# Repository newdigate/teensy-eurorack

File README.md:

# teensy eurorack audio shield 

[![built with kicad](https://img.shields.io/badge/project-v5.1.6-brightgreen.svg?label=kicad&colorA=555555&colorB=8a8fff&logo=
)](https://kicad.org/)

Sponsored by:

**open source [hardware](hardware) and [software](https://github.com/newdigate/teensy-eurorack-software) for a 30-channel (14 in / 16 out) 16-bit analog [teensy 4.1](https://www.pjrc.com/store/teensy40.html "teensy 4.1 board") eurorack shield** 

* add peripherals to extend your [teensy 4.1](https://www.pjrc.com/store/teensy40.html "teensy 4.1 board") to interface with 
  * analog line audio (6 in / 8 out)
  * analog control voltages (8 in / 8 out: -10 to +10 volts)
  * midi in/out
  * microSD socket breakout
  * USB-A host and USB-B devices
  * 4 potentiometers, 3 encoders w/switch
* online designer [teensy eurorack audio gui](https://newdigate.github.io/teensy-eurorack-audio-gui) [^](https://github.com/newdigate/teensy-eurorack-audio-gui)

# updates 
  * 14 August 2021 : software and examples have moved to this repo [newdigate/teensy-eurorack-software](https://github.com/newdigate/teensy-eurorack-software)

# contents
* [sponsor](#sponsor)
* [specifications](#specifications)
* [license](#license)
* [open source software-stack](#open-source-software-stack)
* [build](#build)
  * [order pcbs](#order-pcbs)
  * [sourcing parts](#sourcing-parts)
    * [mouser boms](#mouser-boms)
    * [parts not on mouser boms](#parts-not-on-mouser-boms)
  * [interactive html boms online](#interactive-html-boms-online)
* [source code](#source-code)
* [improvements](#improvements)
* [printed circuit boards](#printed-circuit-boards)
  * [mainboard](#mainboard)
  * [breakout board](#breakout-board)
* [schematics](#schematics)  
* [panel design](#panel-design)  
* [assembly technical drawings](#assembly-technical-drawings)
* [youtube videos](#youtube-videos)
* [versions](#versions)
* [todo](#todo)
* [continuous-integration](#continuous-integration)
* [credits](#credits)
* [sponsored by](#sponsored-by)

# sponsor
* [patreon/teensy_eurorack](https://www.patreon.com/teensy_eurorack)
* paypal.me: [paypal.me/nicnewdigate](https://paypal.me/nicnewdigate)

# specifications
* **microcontrollers:** 
  * 600 Mhz ARM cortex m7 ( [teensy 4.1 board](https://www.pjrc.com/store/teensy41.html "teensy 4.1 board") )
* **audio:** multi-channel audio codec ( 6-in / 8-out 24-bit sound card - [CS42448](https://statics.cirrus.com/pubs/proDatasheet/CS42448_F5.pdf) )
  * *the audio codec circuit originally started as a discussion on quad audio channel outputs and a pcb design integrating teensy and cs42448 from Paul Stoffregen on [pjrc forum](https://forum.pjrc.com/threads/41371-Quad-channel-output-on-Teensy-3-6?p=138828&viewfull=1#post138828)*
* **analog control voltage ins/outs:** -10V to 10V 16bit/sample, 8 x inputs and 8 x outputs ( [ad7606](https://www.analog.com/media/en/technical-documentation/data-sheets/ad7606_7606-6_7606-4.pdf), 2x [ad5754](https://www.analog.com/media/en/technical-documentation/data-sheets/AD5724_5734_5754.pdf) )
* **display:** ST7735 128x128 16bit-color tft display
* **breakouts:** 
  * microSD card socket, 
  * USB host/device, 
  * midi in/out, 
  * knobs (4 x pots, 3 x encoders w/switch)
* **panel:** 24HP aluminium panel mounted for eurorack case
* **programability**: 
  * write arduino compatible c/c++ firmware & program using arduino/teensyduino
  * arm gnu toolchain [downloads](https://developer.arm.com/tools-and-software/open-source-software/developer-tools/gnu-toolchain/gnu-rm/downloads)
  * teensy [audio library](https://www.pjrc.com/teensy/gui/)

# license
* All artifacts are MIT license unless otherwise specified on a per file basis.

# open source software stack
* All [schematics](hardware/CIRCUITS.md) and boards are created using [Kicad](https://kicad.org/) 
* All mechanical designs are created using [FreeCAD](https://github.com/FreeCAD/FreeCAD)
* Some images have been rendered using [Blender 2.81](https://www.blender.org/)

# build
## order pcbs
* Use these gerber files to order 3 pcboards
  * the uSD-card extender should be about 0.6mm - 0.8mm thick
  * if you're using solder paste, you'll need to order the stencils of the bottom-side of main- and breakout boards.   
  
* [gerbers-breakout.zip](https://github.com/newdigate/teensy-eurorack/raw/master/hardware/gerbers/gerbers-breakout.zip)
* [gerbers-mainboard.zip](https://github.com/newdigate/teensy-eurorack/raw/master/hardware/gerbers/gerbers-mainboard.zip)
* [gerbers-uSD_extender_male.zip](https://github.com/newdigate/teensy-eurorack/raw/master/hardware/gerbers/gerbers-uSD_extender_male.zip)

## sourcing parts
Most parts are available from mouser.com - you can use the mouser BOMs below as a template to create an order. 

### mouser boms
* [mainboard](https://eu.mouser.com/ProjectManager/ProjectDetail.aspx?AccessID=e554cc1725)
* [breakoutboard](https://www.mouser.com/ProjectManager/ProjectDetail.aspx?AccessID=76e89a9e69)
### parts not on mouser boms
* panel: 
  * order from Front Panel Express: [.fpd](https://github.com/newdigate/teensy-eurorack/tree/master/hardware/panel/fpd)
    * for US: download [Front Panel Express](https://www.frontpanelexpress.com)
    * for Europe: download [Front Panel Designer](https://www.schaeffer-ag.de/en/front-panel-designer)
  * CNC your own with [FreeCad](https://www.freecadweb.org/downloads.php): [panel.FCStd](https://github.com/newdigate/teensy-eurorack/blob/master/hardware/panel/panel.FCStd) 
* mainboard:
  * 2.54mm pitch pin headers and sockets
    * J28: Eurorack power header: either male or female (2 x 8), I use female as my eurorack power (tip top) has male connectors. 
* breakout:
  * uSD card socket: [pjs008u-3000-0 yamaichi](https://octopart.com/pjs008u-3000-0-yamaichi-20649952?r=sp)
  * display: ST7735 (1.44 inch TFT LCD ST7735 SPI display module 128*128 8pin 65K color)

  * 16 x thonkiconns: [PJ398SM](https://www.thonk.co.uk/shop/thonkiconn)
  * 4 x 9mm snap-in pots: [alpha-9mm-pots](https://www.thonk.co.uk/shop/alpha-9mm-pots/) - You want linear (B-series) not audio (A-series) B5K or B10K should be ideal.
  * 3 x rotary encoders w/switches: Half axis (D-shaft) rotary encoder, handle/axis length: 20mm, EC11/EC12 digital potentiometer with switch - 5Pin

**Update**: USB-A-S-X-X-VT is no longer available. [Amphenol Commercial Products GSB11111ALF](https://mou.sr/3OmC2OO) looks like it may be a good replacement.

## interactive html boms online
  * [mainboard](https://newdigate.github.io/teensy-eurorack/teensy-eurorack)
  * [breakoutboard](https://newdigate.github.io/teensy-eurorack/teensy-eurorack-breakout)

# source code
 * Teensy Audio library drivers for ad5754, ad7606 via SPI
   * [teensy-audio-ad5754-ad7606](https://github.com/newdigate/teensy-audio-ad5754-ad7606)
 * simple standard midi file reader 
   * [midi-smf-reader](https://github.com/newdigate/midi-smf-reader)
 * generic sequencer
   * [teensy-quencer](https://github.com/newdigate/teensy-quencer)
 * variable rate playback
   * [teensy-variable-playback](https://github.com/newdigate/teensy-variable-playback)
 * oscilliscope and x/y scope display components
   * [teensy-audio-libtftscope](https://github.com/newdigate/teensy-audio-libtftscope)
 * cmake macros for compiling c++ for arm cortex 
   * [teensy-cmake-macros](https://github.com/newdigate/teensy-cmake-macros)
 * Audio level and CV level meters 
   * [teensy-audio-display-components](https://github.com/newdigate/teensy-audio-display-components)

# improvements
At this point Im just focusing on finalising/polishing the current version, but there are some improvements I'd like to make at some point.
* add 4x jack sockets for analog output of knobs on breakout board. 
* use 3.5mm jack sockets (as well as standard midi din connectors) for midi in and out. 
* switch to active audio input and output circuitry, allow switchable 0dB / 12dB gain, for guitar signals.
* let me know if you're think there something else that can be improved, added, removed. 

There is a journal of my progress (its a bit out of date, sorry) - [journal.md](hardware/JOURNAL.md) 

**What you can do if you like to see progress with this project?**
* [#sponsor](#sponsor)...
* star this repository (means you need a github account - go for it!!)
* subscribe [Nic N on youtube](https://www.youtube.com/channel/UChMicDp8wUXYzBhEN-Wvb5g) 
* download kicad and freecad, clone this repo, make improvements, commit & send pull-requests, and raise issues...

# printed circuit boards
## [mainboard](hardware/boards/mainboard) 
* standard double layer printed circuit board
  * thinkness: 1.6mm  
  * minimum trace: 6 mil
  * minimum clearance: 6 mil
  * dimension: 118mm*102mm
* socket to connect teensy 4.0 board
* cs42448 audio codec 
* 3 x stereo 6.35mm TRS jack inputs
* 4 x stereo 6.35mm TRS jack outputs
* pin sockets to connect breakout board

## breakout board
* 2 layer printed circuit board
  * thinkness: 1.6mm  
  * minimum trace: 6 mil
  * minimum clearance: 6 mil
  * dimension: 110mm*111mm
* 8 x 3.5mm jack socket for analog control voltage inputs
* 8 x 3.5mm jack socket for analog control voltage outputs
* midi in/out DIN sockets
* usb device/host
  * USB-B: USB device mode
  * USB-A: USB host mode
* micro-SD card socket
* 4 x linear pots
* 3 x rotary encoders with switches 

# schematics

# [panel design](hardware/panel)

# assembly technical drawings 

# youtube videos 
* [Nic N](https://www.youtube.com/channel/UChMicDp8wUXYzBhEN-Wvb5g) 
  * [youtube: Assembling custom eurorack audio shield for teensy 4.1](https://www.youtube.com/watch?v=PzaJ3Wq1Fsc)
  * [youtube: Teensy 4.0 eurorack shield design intro](https://www.youtube.com/watch?v=aNUSEszbnYU)
  * [youtube: 0v to 10v control voltage input, output and display using teensy 4.0](https://www.youtube.com/watch?v=5d5x8F7HRko)
  * [youtube: DIY assembly build - teensy 4.0 eurorack audio module](https://www.youtube.com/watch?v=oZzPgpTrEhc)
  * [youtube: assembly teensy eurorack shield](https://www.youtube.com/watch?v=Jx2KgpoT3WY)
  * [youtube: assembly timelapse](https://www.youtube.com/watch?v=s-514rDjirY)
  * [youtube: Eurorack digital audio modules powered by teensy micro-controller](https://www.youtube.com/watch?v=6zt6OF7UOTc)
  * [youtube: side-channel stereo audio separation with teensy 4.0](https://www.youtube.com/watch?v=N0IBevm4hTQ)

# versions
## v2.1 (Saturday 3 April 2021)
* **Improvement**: Mainboard: Tie LRCLK pin 20 to pin40 to sync DAC/ADC sampling w/ audio sampling
* **FIXED**: breakout: add 1k pull-up resistor to MIDI rx pin
* mainboard: silkscreen: add Kicad OpenSourceHardware logo
* breakout: silkscreen: add Kicad OpenSourceHardware logo

## v2.0.3 (Saturday 13/02/2021)
* breakout: st7735 display changed vcc, reset, backlight from 5v to 3v3.

## v2.0.2 (31/01/2021)
* Mainboard: spaced out traces as there appeared to be some interference under certain circumstances.

## v2.0.1 (27/01/2021) 
* Mainboard: add daisy chain TX/RX connector on back side to communicate between multiple boards
* Breakout board: changed back to double layer board.

## v2.0.0(b)
* Breakout board: Corrected polarity of +-12V pin headers on breakout board (ouch!!!)
* change ADC to use external 2.5v voltage reference, same as DAC voltage reference now 

## v2.0.0
* SPI: separated ADC, DAC from display: 
  * st7735 display has its own dedicated SPI - (SPI0, stays the same)
  * ADC / DAC are now sharing SPI1
* integrated ADC and DAC into teensy audio library.
* added one more ad5754 DAC for total of 8 control voltage analog output channels

## v1.9.1b
* mainboard: correction: reconnected LRCLK to codec.

## v1.9.1
* connected DAC_SCK output (pin 19) to pin 31
  * allow cable select to be asserted on minor spi data cycle after every 24 or 48 spi clock cycles, using interrupt on pin 31.
    * hopefully this will allow DMA spi transfers to AD5754 and which will make integration with teensy audio library much easier

## v1.9 
updated to teesy 4.1 and improvements to make easier to build
* updated from teensy 4.0 to teensy 4.1
* schematic, footprint and pcb clean-up 
  * replaced footprints imported from eagle with native kicad footprints
* removed atmel samd21 and gpio ICs
* replaced gpio with AD5754 (extra 4 DAC channels)
* replaced RGB encoders with regular encoders
* replaced analog-GND-to-digital-GND footprint with a 0805 zero ohm resistor footprint. (DRC checks can pass now...)
* (temporarily) removed serial TX/RX to unused eurorack power pins
  
# todo 
- [x] ~~finalize design / circuits / boards~~
- [x] ~~order~~ (v.2.1)
- [x] ~~assemble~~
- [x] ~~testing~~
  - [x] ~~CS42448 audio codec~~
    - [x] ~~Audio input~~
    - [x] ~~Audio output~~
  - [x] ~~control voltage input~~
  - [x] ~~control voltage output~~
  - [x] ~~usb host~~
  - [x] ~~usb device~~
  - [x] ~~midi in~~
  - [x] ~~midi out~~
  - [x] ~~st7735 display~~
  - [x] ~~sd card extension & adapter~~
- [ ] Document 
  - [ ] order & build process
  - [ ] software process
- [ ] Firmware

# continuous-integration 
* testing automated build and packaging 
* [github.com/pwuertz/kicad_picknplace_assistant](https://github.com/pwuertz/kicad_picknplace_assistant)
* [github.com/productize/kicad-automation-scripts](https://github.com/productize/kicad-automation-scripts)
* [InteractiveHtmlBom](https://github.com/openscopeproject/InteractiveHtmlBom) by [openscopeproject](https://github.com/openscopeproject)

# credits 
* https://github.com/dgouramanis/usdextendercable

# sponsored by
Massive thanks to these generous people who have provided support!
* Hannes Schnaitter
* Daniel Hengeveld [thedaniel on github](https://github.com/thedaniel)
* Derek Brost
* Martin Eigel
* Morgan Massens

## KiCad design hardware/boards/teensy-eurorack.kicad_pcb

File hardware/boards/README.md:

# boards
 * [mainboard](#mainboard)
 * [breakout](#breakout)
 
All circuit boards are standard double layer boards with minimum 6 mil clearance and 6 mil traces. 

I have been using jlcpcb to fabricate my circuit boards.  

## [mainboard](mainboard) 

[mainboard design files](mainboard)

### [breakout](knobs-controller) 

[breakout design files](knobs-controller)

# assembly technical drawings

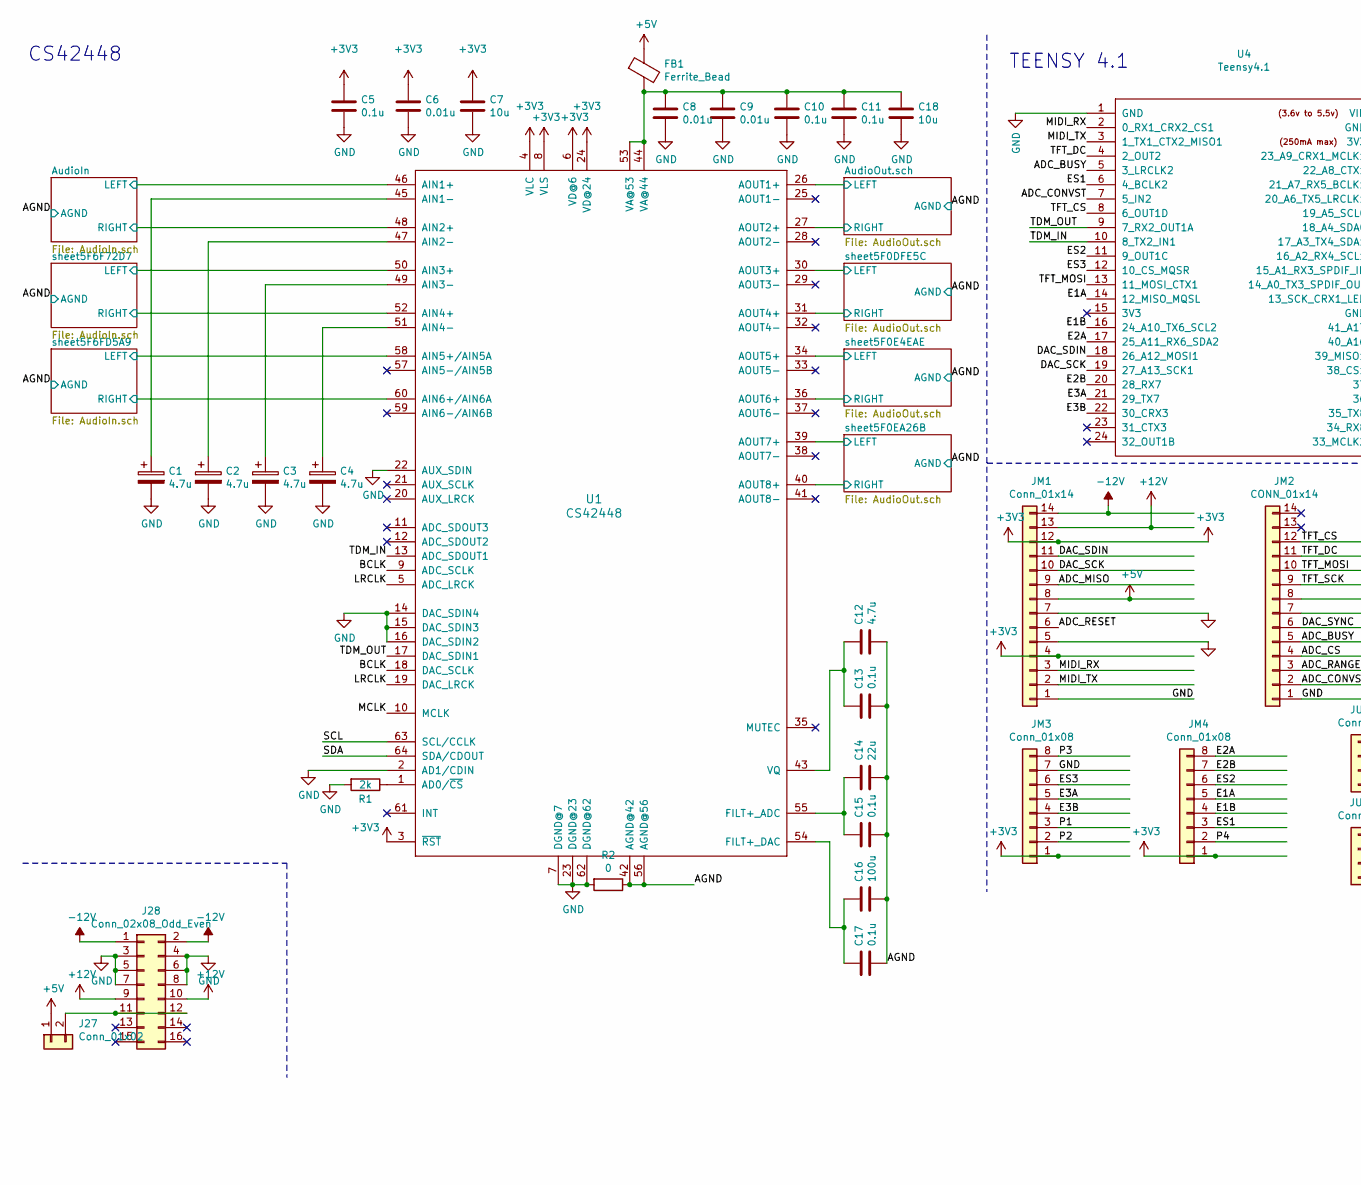
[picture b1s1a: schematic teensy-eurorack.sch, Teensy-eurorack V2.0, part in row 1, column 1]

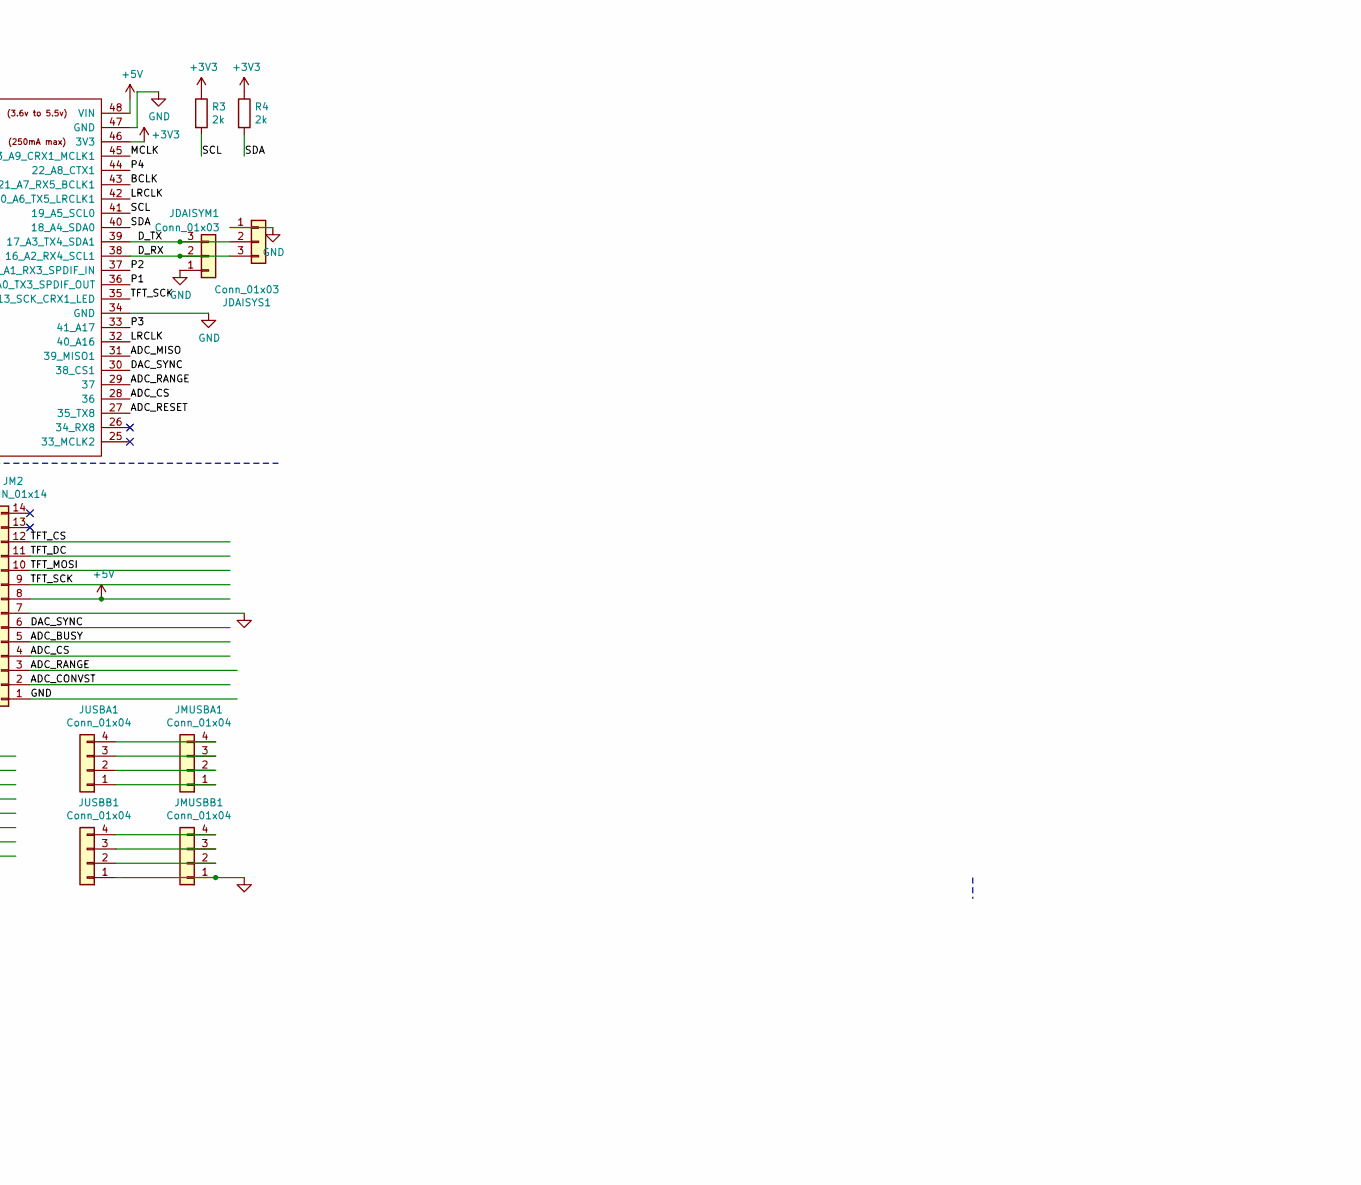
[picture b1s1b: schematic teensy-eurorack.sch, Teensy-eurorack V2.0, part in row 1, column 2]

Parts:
C1, C2, C3, C4: 4.7u; CP_Radial_D5.0mm_P2.50mm
C5, C10, C11, C13, C15, C17: 0.1u; C_0805_2012Metric
C6, C8, C9: 0.01u; C_0805_2012Metric
C7, C18: 10u; C_0805_2012Metric
C12: 4.7u; C_0805_2012Metric
C14: 22u; C_0805_2012Metric
C16: 100u; C_1206_3216Metric
FB1: Ferrite_Bead; L_0603_1608Metric
J27: Conn_01x02; PinHeader_1x02_P2.54mm_Vertical
J28: Conn_02x08_Odd_Even; PinHeader_2x08_P2.54mm_Vertical
JDAISYM1: Conn_01x03; PinHeader_1x03_P2.54mm_Vertical
JDAISYS1: Conn_01x03; PinHeader_1x03_P2.54mm_Vertical
JM1: Conn_01x14; PinHeader_1x14_P2.54mm_Vertical
JM2: CONN_01x14; PinHeader_1x14_P2.54mm_Vertical
JM3, JM4: Conn_01x08; PinHeader_1x08_P2.54mm_Vertical
JMUSBA1: Conn_01x04; PinHeader_1x04_P2.54mm_Vertical
JMUSBB1: Conn_01x04; PinHeader_1x04_P2.54mm_Vertical
JUSBA1: Conn_01x04; PinHeader_1x04_P2.54mm_Vertical
JUSBB1: Conn_01x04; PinHeader_1x04_P2.54mm_Vertical
R1, R3, R4: 2k; R_0805_2012Metric
R2: 0; R_0805_2012Metric
U1: CS42448; LQFP-64_10x10mm_P0.5mm
U4: Teensy4.1; Teensy41_tht

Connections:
+3V3: C5.1, C6.1, C7.1, JM1.4, JM1.12, JM3.1, JM4.1, R3.1, R4.1, U1.3 (~RST~), U1.4 (VLC), U1.6 (VD@6), U1.8 (VLS), U1.24 (VD@24), U4.46 (3V3)
+5V: FB1.1, J27.1, JM1.8, JM2.8, U4.48 (VIN)
+12V: J28.9, J28.10, JM1.13
-12V: J28.1, J28.2, JM1.14
/ADC_BUSY: JM2.5, U4.5 (3_LRCLK2)
/ADC_CONVST: JM2.2, U4.7 (5_IN2)
/ADC_CS: JM2.4, U4.28 (36)
/ADC_MISO: JM1.9, U4.31 (39_MISO1)
/ADC_RANGE: JM2.3, U4.29 (37)
/ADC_RESET: JM1.6, U4.27 (35_TX8)
/AGND: C12.2, C13.2, C14.2, C15.2, C16.2, C17.2, R2.1, U1.42 (AGND@42), U1.56 (AGND@56); also elsewhere on the board
/AudioIn/LEFT: U1.46 (AIN1+); also elsewhere on the board
/AudioIn/RIGHT: U1.48 (AIN2+); also elsewhere on the board
/AudioOut.sch/LEFT: U1.26 (AOUT1+); also elsewhere on the board
/AudioOut.sch/RIGHT: U1.27 (AOUT2+); also elsewhere on the board
/BCLK: U1.9 (ADC_SCLK), U1.18 (DAC_SCLK), U4.43 (21_A7_RX5_BCLK1)
/DAC_SCK: JM1.10, U4.19 (27_A13_SCK1)
/DAC_SDIN: JM1.11, U4.18 (26_A12_MOSI1)
/DAC_SYNC: JM2.6, U4.30 (38_CS1)
/D_RX: JDAISYM1.2, JDAISYS1.3, U4.38 (16_A2_RX4_SCL1)
/D_TX: JDAISYM1.3, JDAISYS1.2, U4.39 (17_A3_TX4_SDA1)
/E1A: JM4.5, U4.14 (12_MISO_MQSL)
/E1B: JM4.4, U4.16 (24_A10_TX6_SCL2)
/E2A: JM4.8, U4.17 (25_A11_RX6_SDA2)
/E2B: JM4.7, U4.20 (28_RX7)
/E3A: JM3.5, U4.21 (29_TX7)
/E3B: JM3.4, U4.22 (30_CRX3)
/ES1: JM4.3, U4.6 (4_BCLK2)
/ES2: JM4.6, U4.11 (9_OUT1C)
/ES3: JM3.6, U4.12 (10_CS_MQSR)
/LRCLK: U1.5 (ADC_LRCK), U1.19 (DAC_LRCK), U4.32 (40_A16), U4.42 (20_A6_TX5_LRCLK1)
/MCLK: U1.10 (MCLK), U4.45 (23_A9_CRX1_MCLK1)
/MIDI_RX: JM1.3, U4.2 (0_RX1_CRX2_CS1)
/MIDI_TX: JM1.2, U4.3 (1_TX1_CTX2_MISO1)
/P1: JM3.3, U4.36 (14_A0_TX3_SPDIF_OUT)
/P2: JM3.2, U4.37 (15_A1_RX3_SPDIF_IN)
/P3: JM3.8, U4.33 (41_A17)
/P4: JM4.2, U4.44 (22_A8_CTX1)
/SCL: R3.2, U1.63 (SCL/CCLK), U4.41 (19_A5_SCL0)
/SDA: R4.2, U1.64 (SDA/CDOUT), U4.40 (18_A4_SDA0)
/TDM_IN: U1.13 (ADC_SDOUT1), U4.10 (8_TX2_IN1)
/TDM_OUT: U1.17 (DAC_SDIN1), U4.9 (7_RX2_OUT1A)
/TFT_CS: JM2.12, U4.8 (6_OUT1D)
/TFT_DC: JM2.11, U4.4 (2_OUT2)
/TFT_MOSI: JM2.10, U4.13 (11_MOSI_CTX1)
/TFT_SCK: JM2.9, U4.35 (13_SCK_CRX1_LED)
/sheet5F0DFE5C/LEFT: U1.30 (AOUT3+); also elsewhere on the board
/sheet5F0DFE5C/RIGHT: U1.31 (AOUT4+); also elsewhere on the board
/sheet5F0E4EAE/LEFT: U1.34 (AOUT5+); also elsewhere on the board
/sheet5F0E4EAE/RIGHT: U1.36 (AOUT6+); also elsewhere on the board
/sheet5F0EA26B/LEFT: U1.39 (AOUT7+); also elsewhere on the board
/sheet5F0EA26B/RIGHT: U1.40 (AOUT8+); also elsewhere on the board
/sheet5F6F72D7/LEFT: U1.50 (AIN3+); also elsewhere on the board
/sheet5F6F72D7/RIGHT: U1.52 (AIN4+); also elsewhere on the board
/sheet5F6FD5A9/LEFT: U1.58 (AIN5+/AIN5A); also elsewhere on the board
/sheet5F6FD5A9/RIGHT: U1.60 (AIN6+/AIN6A); also elsewhere on the board
GND: C1.2, C2.2, C3.2, C4.2, C5.2, C6.2, C7.2, C8.2, C9.2, C10.2, C11.2, C18.2, J28.3, J28.4, J28.5, J28.6, J28.7, J28.8, JDAISYM1.1, JDAISYS1.1, JM1.1, JM1.5, JM1.7, JM2.1, JM2.7, JM3.7, JMUSBB1.1, JUSBB1.1, R1.2, R2.2, U1.2 (AD1/CDIN), U1.7 (DGND@7), U1.14 (DAC_SDIN4), U1.15 (DAC_SDIN3), U1.16 (DAC_SDIN2), U1.22 (AUX_SDIN), U1.23 (DGND@23), U1.62 (DGND@62), U4.1 (GND), U4.34 (GND), U4.47 (GND)
unnamed: C1.1, U1.45 (AIN1-)
unnamed: C2.1, U1.47 (AIN2-)
unnamed: C3.1, U1.49 (AIN3-)
unnamed: C4.1, U1.51 (AIN4-)
unnamed: C8.1, C9.1, C10.1, C11.1, C18.1, FB1.2, U1.44 (VA@44), U1.53 (VA@53)
unnamed: C12.1, C13.1, U1.43 (VQ)
unnamed: C14.1, C15.1, U1.55 (FILT+_ADC)
unnamed: C16.1, C17.1, U1.54 (FILT+_DAC)
unnamed: J27.2, J28.11, J28.12
unnamed: JMUSBA1.1, JUSBA1.1
unnamed: JMUSBA1.2, JUSBA1.2
unnamed: JMUSBA1.3, JUSBA1.3
unnamed: JMUSBA1.4, JUSBA1.4
unnamed: JMUSBB1.2, JUSBB1.2
unnamed: JMUSBB1.3, JUSBB1.3
unnamed: JMUSBB1.4, JUSBB1.4
unnamed: R1.1, U1.1 (AD0/~CS~)

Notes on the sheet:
TEENSY 4.1
CS42448

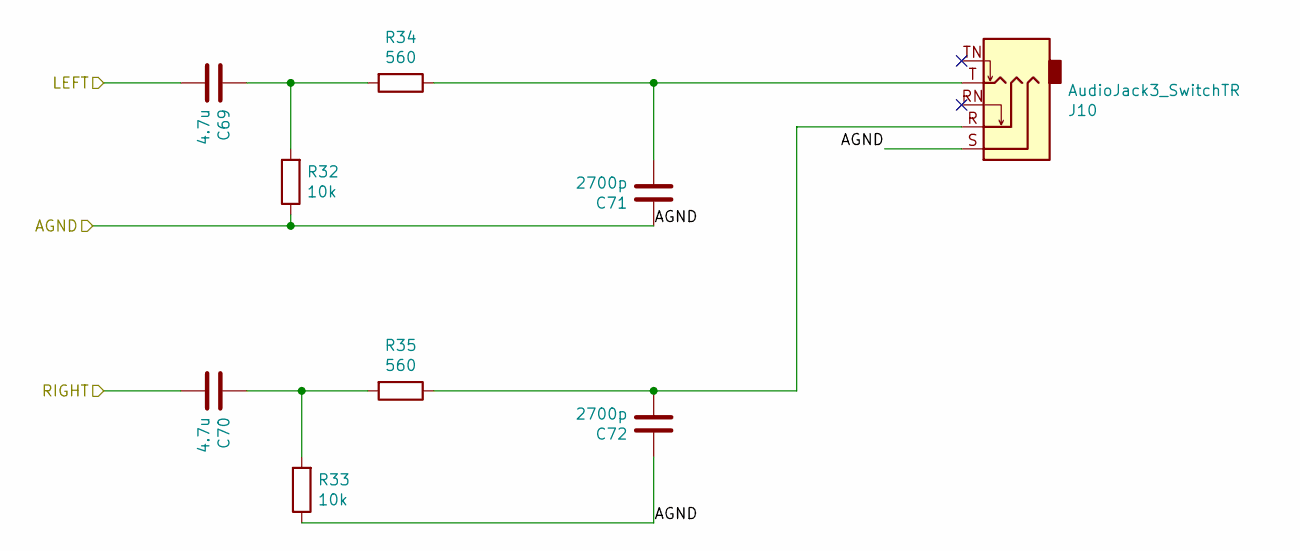
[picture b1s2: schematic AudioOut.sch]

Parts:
C45, C46: 4.7u; C_0805_2012Metric
C47, C48: 2700p; C_0805_2012Metric
J4: AudioJack3_SwitchTR; ACJS-MV5
R8, R9: 10k; R_0805_2012Metric
R10, R11: 560; R_0805_2012Metric

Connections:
/AGND: C47.1, C48.1, J4.S, R8.1, R9.1; also elsewhere on the board
/AudioOut.sch/LEFT: C45.2; also elsewhere on the board
/AudioOut.sch/RIGHT: C46.2; also elsewhere on the board
unnamed: C45.1, R8.2, R10.2
unnamed: C46.1, R9.2, R11.2
unnamed: C47.2, J4.T, R10.1
unnamed: C48.2, J4.R, R11.1

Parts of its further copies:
C49, C50, C53, C54, C69, C70: 4.7u; C_0805_2012Metric
C51, C52, C55, C56, C71, C72: 2700p; C_0805_2012Metric
J5, J6, J10: AudioJack3_SwitchTR; ACJS-MV5
R12, R13, R16, R17, R32, R33: 10k; R_0805_2012Metric
R14, R15, R18, R19, R34, R35: 560; R_0805_2012Metric

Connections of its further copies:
/AGND: C51.1, C52.1, C55.1, C56.1, C71.1, C72.1, J5.S, J6.S, J10.S, R12.1, R13.1, R16.1, R17.1, R32.1, R33.1; also elsewhere on the board
/sheet5F0DFE5C/LEFT: C49.2; also elsewhere on the board
/sheet5F0DFE5C/RIGHT: C50.2; also elsewhere on the board
/sheet5F0E4EAE/LEFT: C69.2; also elsewhere on the board
/sheet5F0E4EAE/RIGHT: C70.2; also elsewhere on the board
/sheet5F0EA26B/LEFT: C53.2; also elsewhere on the board
/sheet5F0EA26B/RIGHT: C54.2; also elsewhere on the board
unnamed: C49.1, R12.2, R14.2
unnamed: C50.1, R13.2, R15.2
unnamed: C51.2, J5.T, R14.1
unnamed: C52.2, J5.R, R15.1
unnamed: C53.1, R16.2, R18.2
unnamed: C54.1, R17.2, R19.2
unnamed: C55.2, J6.T, R18.1
unnamed: C56.2, J6.R, R19.1
unnamed: C69.1, R32.2, R34.2
unnamed: C70.1, R33.2, R35.2
unnamed: C71.2, J10.T, R34.1
unnamed: C72.2, J10.R, R35.1

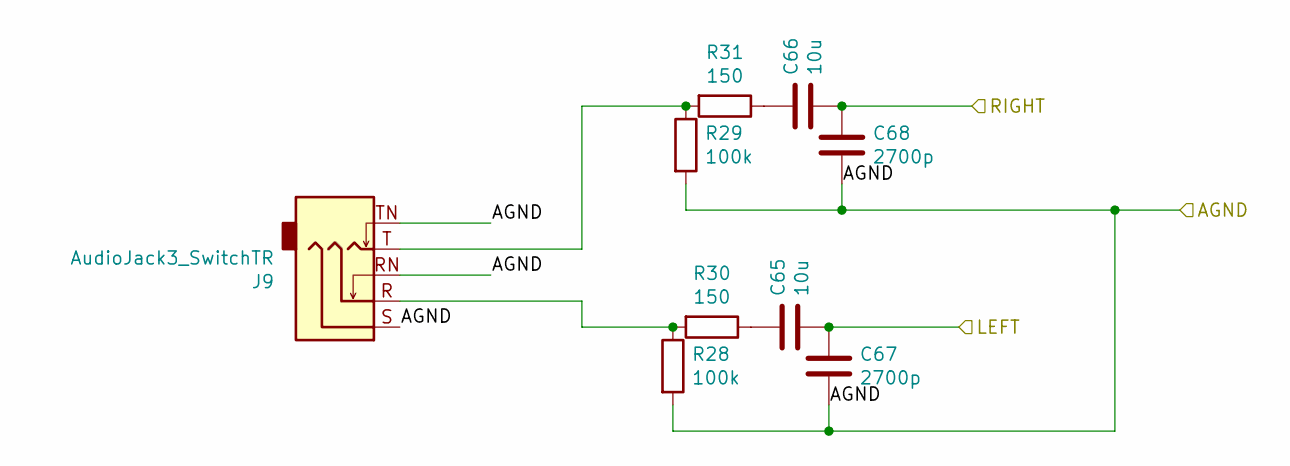
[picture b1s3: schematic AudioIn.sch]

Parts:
C65, C66: 10u; C_0805_2012Metric
C67, C68: 2700p; C_0805_2012Metric
J9: AudioJack3_SwitchTR; ACJS-MV5
R28, R29: 100k; R_0805_2012Metric
R30, R31: 150; R_0805_2012Metric

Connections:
/AGND: C67.2, C68.2, J9.RN, J9.S, J9.TN, R28.2, R29.2; also elsewhere on the board
/AudioIn/LEFT: C65.2, C67.1; also elsewhere on the board
/AudioIn/RIGHT: C66.2, C68.1; also elsewhere on the board
unnamed: C65.1, R30.1
unnamed: C66.1, R31.1
unnamed: J9.R, R28.1, R30.2
unnamed: J9.T, R29.1, R31.2

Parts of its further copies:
C57, C58, C61, C62: 10u; C_0805_2012Metric
C59, C60, C63, C64: 2700p; C_0805_2012Metric
J7, J8: AudioJack3_SwitchTR; ACJS-MV5
R20, R21, R24, R25: 100k; R_0805_2012Metric
R22, R23, R26, R27: 150; R_0805_2012Metric

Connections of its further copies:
/AGND: C59.2, C60.2, C63.2, C64.2, J7.RN, J7.S, J7.TN, J8.RN, J8.S, J8.TN, R20.2, R21.2, R24.2, R25.2; also elsewhere on the board
/sheet5F6F72D7/LEFT: C57.2, C59.1; also elsewhere on the board
/sheet5F6F72D7/RIGHT: C58.2, C60.1; also elsewhere on the board
/sheet5F6FD5A9/LEFT: C61.2, C63.1; also elsewhere on the board
/sheet5F6FD5A9/RIGHT: C62.2, C64.1; also elsewhere on the board
unnamed: C57.1, R22.1
unnamed: C58.1, R23.1
unnamed: C61.1, R26.1
unnamed: C62.1, R27.1
unnamed: J7.R, R20.1, R22.2
unnamed: J7.T, R21.1, R23.2
unnamed: J8.R, R24.1, R26.2
unnamed: J8.T, R25.1, R27.2

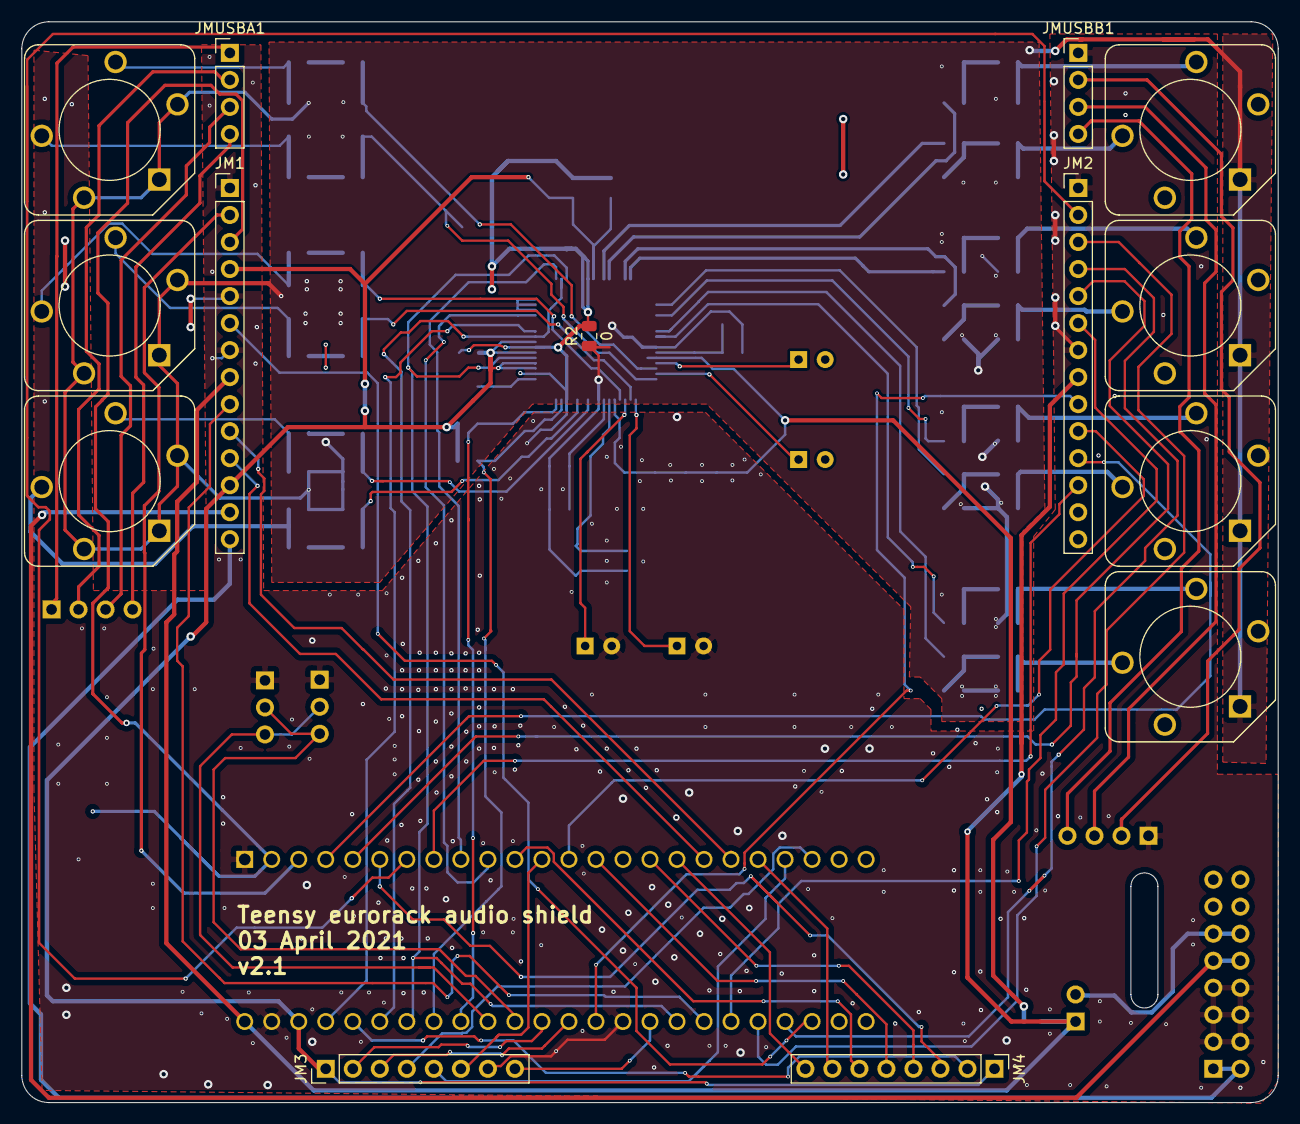
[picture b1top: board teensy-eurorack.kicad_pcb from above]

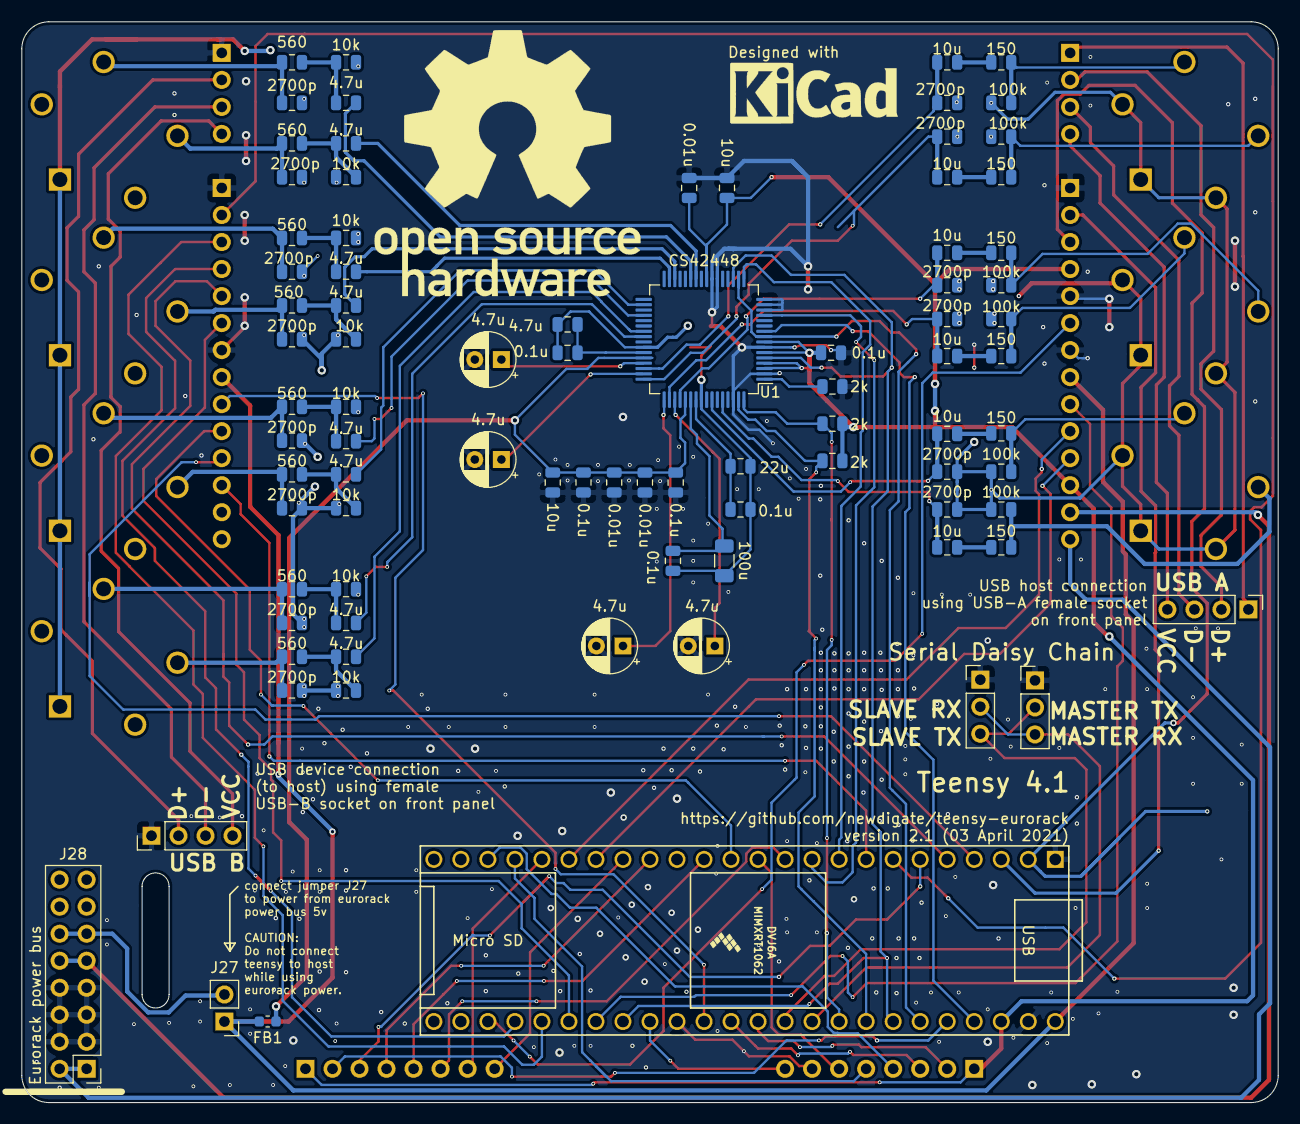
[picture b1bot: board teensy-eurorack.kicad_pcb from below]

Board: 2 copper layers, 118.1 x 101.6 mm, 100 parts (86 on the bottom side), 102 nets.

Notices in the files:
parts and their libraries:
SparkFun-Aesthetics: Licensing: Creative Commons ShareAlike 4.0 International - https://creativecommons.org/licenses/by-sa/4.0
